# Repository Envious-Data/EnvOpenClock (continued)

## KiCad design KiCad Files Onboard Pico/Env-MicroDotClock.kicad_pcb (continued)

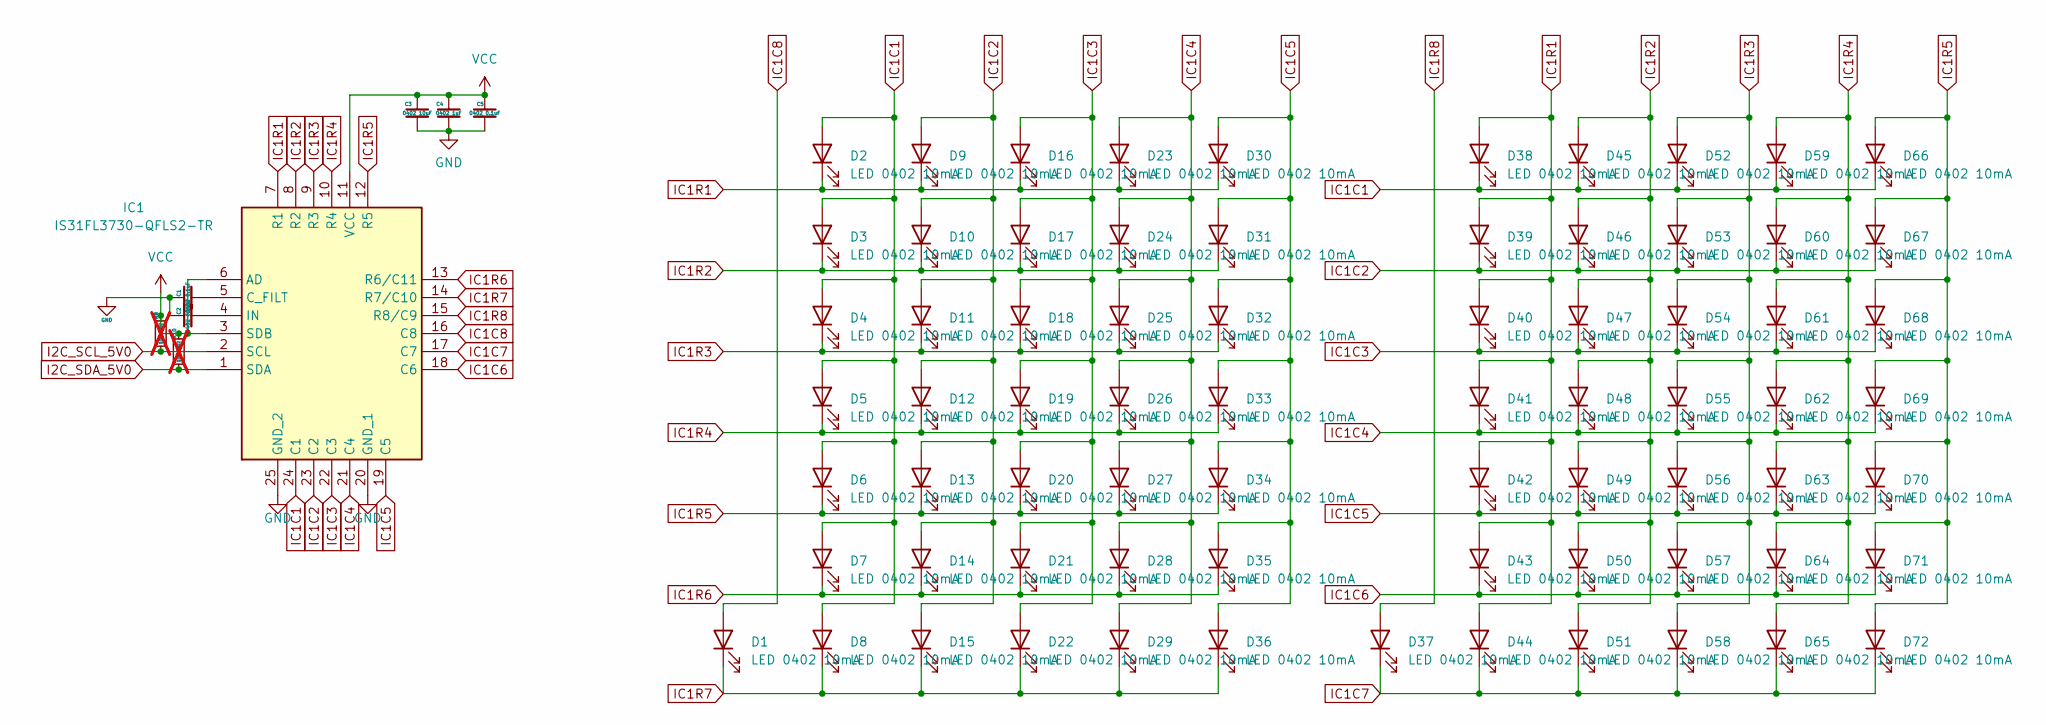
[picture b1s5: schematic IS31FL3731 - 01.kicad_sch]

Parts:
C1, C5: 0402 0.1uF; C_0402_1005Metric
C2: 0402 0.22uF; C_0402_1005Metric
C3: 0402 10uF; C_0402_1005Metric
C4: 0402 1uF; C_0402_1005Metric
D1, D2, D3, D4, D5, D6, D7, D8, D9, D10, D11, D12, D13, D14, D15, D16, D17, D18, D19, D20, D21, D22, D23, D24, D25, D26, D27, D28, D29, D30, D31, D32, D33, D34, D35, D36, D37, D38, D39, D40, D41, D42, D43, D44, D45, D46, D47, D48, D49, D50, D51, D52, D53, D54, D55, D56, D57, D58, D59, D60, D61, D62, D63, D64, D65, D66, D67, D68, D69, D70, D71, D72: LED 0402 10mA; LED_0402_1005Metric
IC1: IS31FL3730-QFLS2-TR; QFN-24-1EP_4x4mm_P0.5mm_EP2.6x2.6mm_ThermalVias; Mouser Part Number 870-IS31FL3730QFLS2R
R8, R10: 10K 0402; R_0402_1005Metric; not fitted

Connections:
GND: C1.1, C2.1, C3.2, C4.2, C5.2, IC1.20 (GND_1), IC1.25 (GND_2); also elsewhere on the board
I2C_SCL_5V0: IC1.2 (SCL), R8.1; also elsewhere on the board
I2C_SDA_5V0: IC1.1 (SDA), R10.1; also elsewhere on the board
IC1C1: D2.2 (A), D3.2 (A), D4.2 (A), D5.2 (A), D6.2 (A), D7.2 (A), D8.2 (A), D38.1 (K), D45.1 (K), D52.1 (K), D59.1 (K), D66.1 (K), IC1.24 (C1)
IC1C2: D9.2 (A), D10.2 (A), D11.2 (A), D12.2 (A), D13.2 (A), D14.2 (A), D15.2 (A), D39.1 (K), D46.1 (K), D53.1 (K), D60.1 (K), D67.1 (K), IC1.23 (C2)
IC1C3: D16.2 (A), D17.2 (A), D18.2 (A), D19.2 (A), D20.2 (A), D21.2 (A), D22.2 (A), D40.1 (K), D47.1 (K), D54.1 (K), D61.1 (K), D68.1 (K), IC1.22 (C3)
IC1C4: D23.2 (A), D24.2 (A), D25.2 (A), D26.2 (A), D27.2 (A), D28.2 (A), D29.2 (A), D41.1 (K), D48.1 (K), D55.1 (K), D62.1 (K), D69.1 (K), IC1.21 (C4)
IC1C5: D30.2 (A), D31.2 (A), D32.2 (A), D33.2 (A), D34.2 (A), D35.2 (A), D36.2 (A), D42.1 (K), D49.1 (K), D56.1 (K), D63.1 (K), D70.1 (K), IC1.19 (C5)
IC1C6: D43.1 (K), D50.1 (K), D57.1 (K), D64.1 (K), D71.1 (K), IC1.18 (C6)
IC1C7: D37.1 (K), D44.1 (K), D51.1 (K), D58.1 (K), D65.1 (K), D72.1 (K), IC1.17 (C7)
IC1C8: D1.2 (A), IC1.16 (C8)
IC1R1: D2.1 (K), D9.1 (K), D16.1 (K), D23.1 (K), D30.1 (K), D38.2 (A), D39.2 (A), D40.2 (A), D41.2 (A), D42.2 (A), D43.2 (A), D44.2 (A), IC1.7 (R1)
IC1R2: D3.1 (K), D10.1 (K), D17.1 (K), D24.1 (K), D31.1 (K), D45.2 (A), D46.2 (A), D47.2 (A), D48.2 (A), D49.2 (A), D50.2 (A), D51.2 (A), IC1.8 (R2)
IC1R3: D4.1 (K), D11.1 (K), D18.1 (K), D25.1 (K), D32.1 (K), D52.2 (A), D53.2 (A), D54.2 (A), D55.2 (A), D56.2 (A), D57.2 (A), D58.2 (A), IC1.9 (R3)
IC1R4: D5.1 (K), D12.1 (K), D19.1 (K), D26.1 (K), D33.1 (K), D59.2 (A), D60.2 (A), D61.2 (A), D62.2 (A), D63.2 (A), D64.2 (A), D65.2 (A), IC1.10 (R4)
IC1R5: D6.1 (K), D13.1 (K), D20.1 (K), D27.1 (K), D34.1 (K), D66.2 (A), D67.2 (A), D68.2 (A), D69.2 (A), D70.2 (A), D71.2 (A), D72.2 (A), IC1.12 (R5)
IC1R6: D7.1 (K), D14.1 (K), D21.1 (K), D28.1 (K), D35.1 (K), IC1.13 (R6/C11)
IC1R7: D1.1 (K), D8.1 (K), D15.1 (K), D22.1 (K), D29.1 (K), D36.1 (K), IC1.14 (R7/C10)
IC1R8: D37.2 (A), IC1.15 (R8/C9)
unnamed: C1.2, IC1.5 (C_FILT)
unnamed: C2.2, IC1.4 (IN)
VCC: C3.1, C4.1, C5.1, IC1.3 (SDB), IC1.6 (AD), IC1.11 (VCC), R8.2, R10.2; also elsewhere on the board

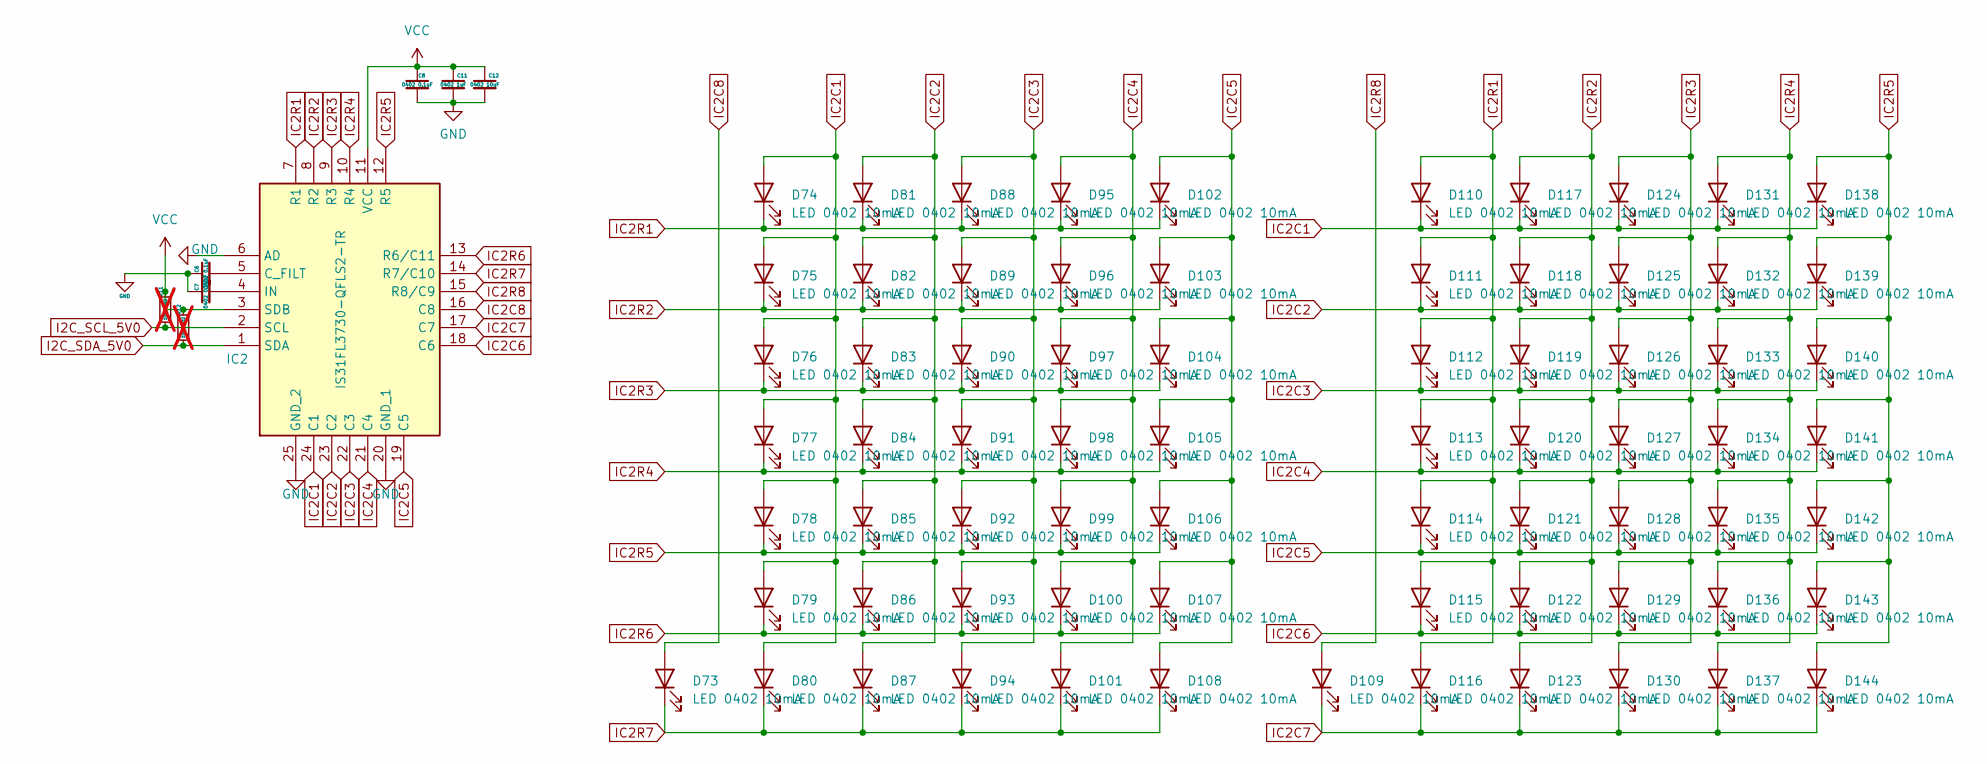
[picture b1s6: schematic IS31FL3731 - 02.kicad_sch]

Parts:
C6, C8: 0402 0.1uF; C_0402_1005Metric
C7: 0402 0.22uF; C_0402_1005Metric
C11: 0402 1uF; C_0402_1005Metric
C12: 0402 10uF; C_0402_1005Metric
D73, D74, D75, D76, D77, D78, D79, D80, D81, D82, D83, D84, D85, D86, D87, D88, D89, D90, D91, D92, D93, D94, D95, D96, D97, D98, D99, D100, D101, D102, D103, D104, D105, D106, D107, D108, D109, D110, D111, D112, D113, D114, D115, D116, D117, D118, D119, D120, D121, D122, D123, D124, D125, D126, D127, D128, D129, D130, D131, D132, D133, D134, D135, D136, D137, D138, D139, D140, D141, D142, D143, D144: LED 0402 10mA; LED_0402_1005Metric
IC2: IS31FL3730-QFLS2-TR; QFN-24-1EP_4x4mm_P0.5mm_EP2.6x2.6mm_ThermalVias; Mouser Part Number 870-IS31FL3730QFLS2R
R11, R12: 10K 0402; R_0402_1005Metric; not fitted

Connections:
GND: C6.1, C7.1, C8.2, C11.2, C12.2, IC2.6 (AD), IC2.20 (GND_1), IC2.25 (GND_2); also elsewhere on the board
I2C_SCL_5V0: IC2.2 (SCL), R11.1; also elsewhere on the board
I2C_SDA_5V0: IC2.1 (SDA), R12.1; also elsewhere on the board
IC2C1: D74.2 (A), D75.2 (A), D76.2 (A), D77.2 (A), D78.2 (A), D79.2 (A), D80.2 (A), D110.1 (K), D117.1 (K), D124.1 (K), D131.1 (K), D138.1 (K), IC2.24 (C1)
IC2C2: D81.2 (A), D82.2 (A), D83.2 (A), D84.2 (A), D85.2 (A), D86.2 (A), D87.2 (A), D111.1 (K), D118.1 (K), D125.1 (K), D132.1 (K), D139.1 (K), IC2.23 (C2)
IC2C3: D88.2 (A), D89.2 (A), D90.2 (A), D91.2 (A), D92.2 (A), D93.2 (A), D94.2 (A), D112.1 (K), D119.1 (K), D126.1 (K), D133.1 (K), D140.1 (K), IC2.22 (C3)
IC2C4: D95.2 (A), D96.2 (A), D97.2 (A), D98.2 (A), D99.2 (A), D100.2 (A), D101.2 (A), D113.1 (K), D120.1 (K), D127.1 (K), D134.1 (K), D141.1 (K), IC2.21 (C4)
IC2C5: D102.2 (A), D103.2 (A), D104.2 (A), D105.2 (A), D106.2 (A), D107.2 (A), D108.2 (A), D114.1 (K), D121.1 (K), D128.1 (K), D135.1 (K), D142.1 (K), IC2.19 (C5)
IC2C6: D115.1 (K), D122.1 (K), D129.1 (K), D136.1 (K), D143.1 (K), IC2.18 (C6)
IC2C7: D109.1 (K), D116.1 (K), D123.1 (K), D130.1 (K), D137.1 (K), D144.1 (K), IC2.17 (C7)
IC2C8: D73.2 (A), IC2.16 (C8)
IC2R1: D74.1 (K), D81.1 (K), D88.1 (K), D95.1 (K), D102.1 (K), D110.2 (A), D111.2 (A), D112.2 (A), D113.2 (A), D114.2 (A), D115.2 (A), D116.2 (A), IC2.7 (R1)
IC2R2: D75.1 (K), D82.1 (K), D89.1 (K), D96.1 (K), D103.1 (K), D117.2 (A), D118.2 (A), D119.2 (A), D120.2 (A), D121.2 (A), D122.2 (A), D123.2 (A), IC2.8 (R2)
IC2R3: D76.1 (K), D83.1 (K), D90.1 (K), D97.1 (K), D104.1 (K), D124.2 (A), D125.2 (A), D126.2 (A), D127.2 (A), D128.2 (A), D129.2 (A), D130.2 (A), IC2.9 (R3)
IC2R4: D77.1 (K), D84.1 (K), D91.1 (K), D98.1 (K), D105.1 (K), D131.2 (A), D132.2 (A), D133.2 (A), D134.2 (A), D135.2 (A), D136.2 (A), D137.2 (A), IC2.10 (R4)
IC2R5: D78.1 (K), D85.1 (K), D92.1 (K), D99.1 (K), D106.1 (K), D138.2 (A), D139.2 (A), D140.2 (A), D141.2 (A), D142.2 (A), D143.2 (A), D144.2 (A), IC2.12 (R5)
IC2R6: D79.1 (K), D86.1 (K), D93.1 (K), D100.1 (K), D107.1 (K), IC2.13 (R6/C11)
IC2R7: D73.1 (K), D80.1 (K), D87.1 (K), D94.1 (K), D101.1 (K), D108.1 (K), IC2.14 (R7/C10)
IC2R8: D109.2 (A), IC2.15 (R8/C9)
unnamed: C6.2, IC2.5 (C_FILT)
unnamed: C7.2, IC2.4 (IN)
VCC: C8.1, C11.1, C12.1, IC2.3 (SDB), IC2.11 (VCC), R11.2, R12.2; also elsewhere on the board

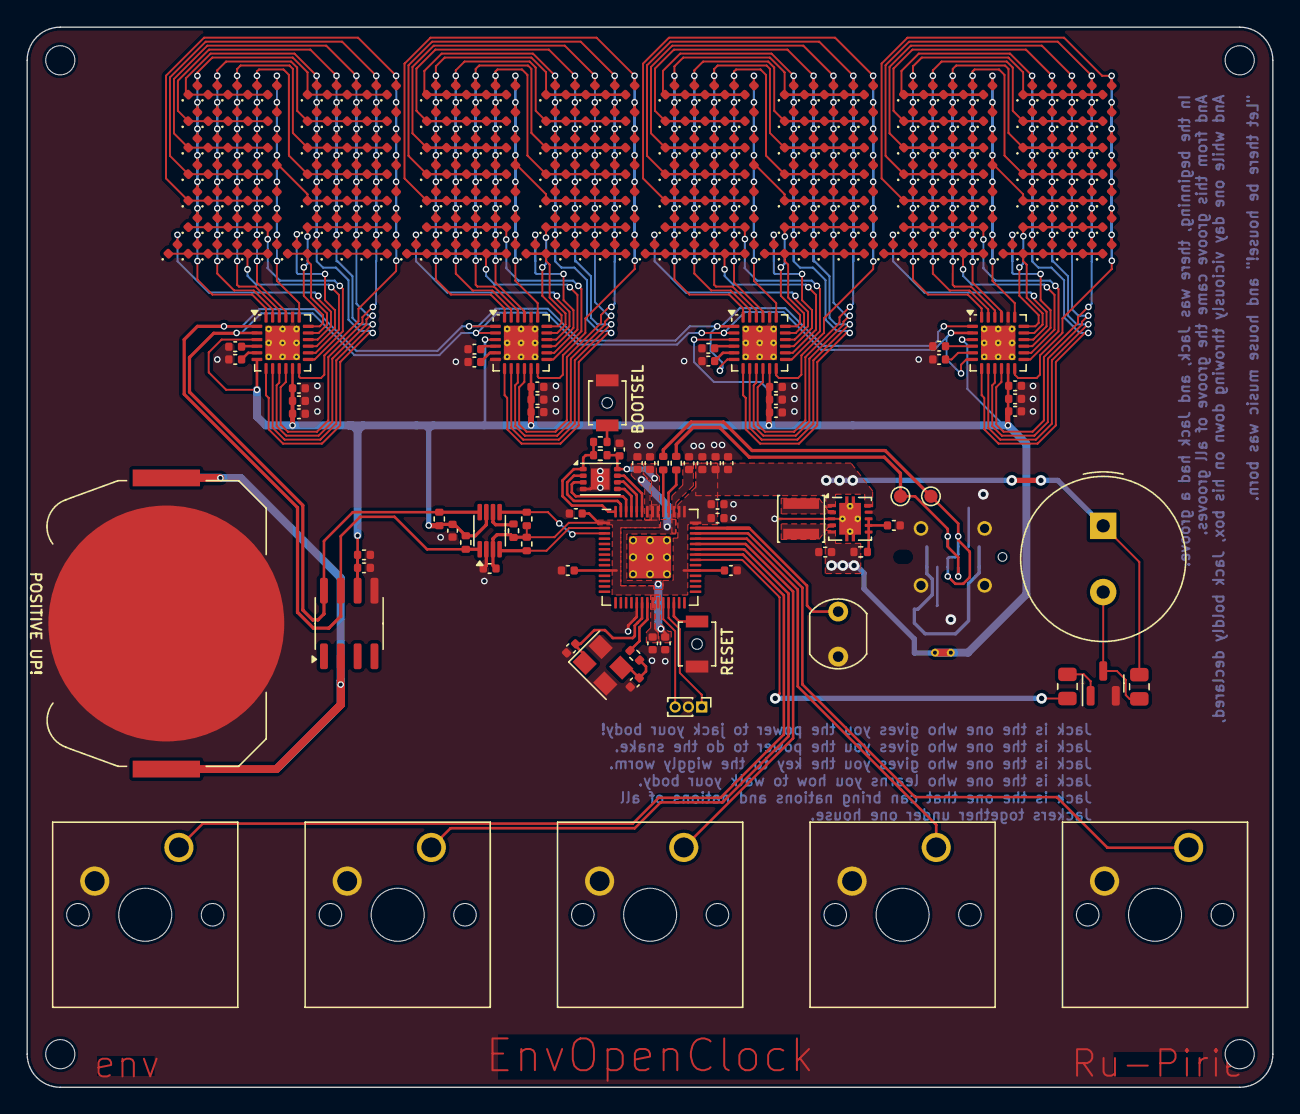
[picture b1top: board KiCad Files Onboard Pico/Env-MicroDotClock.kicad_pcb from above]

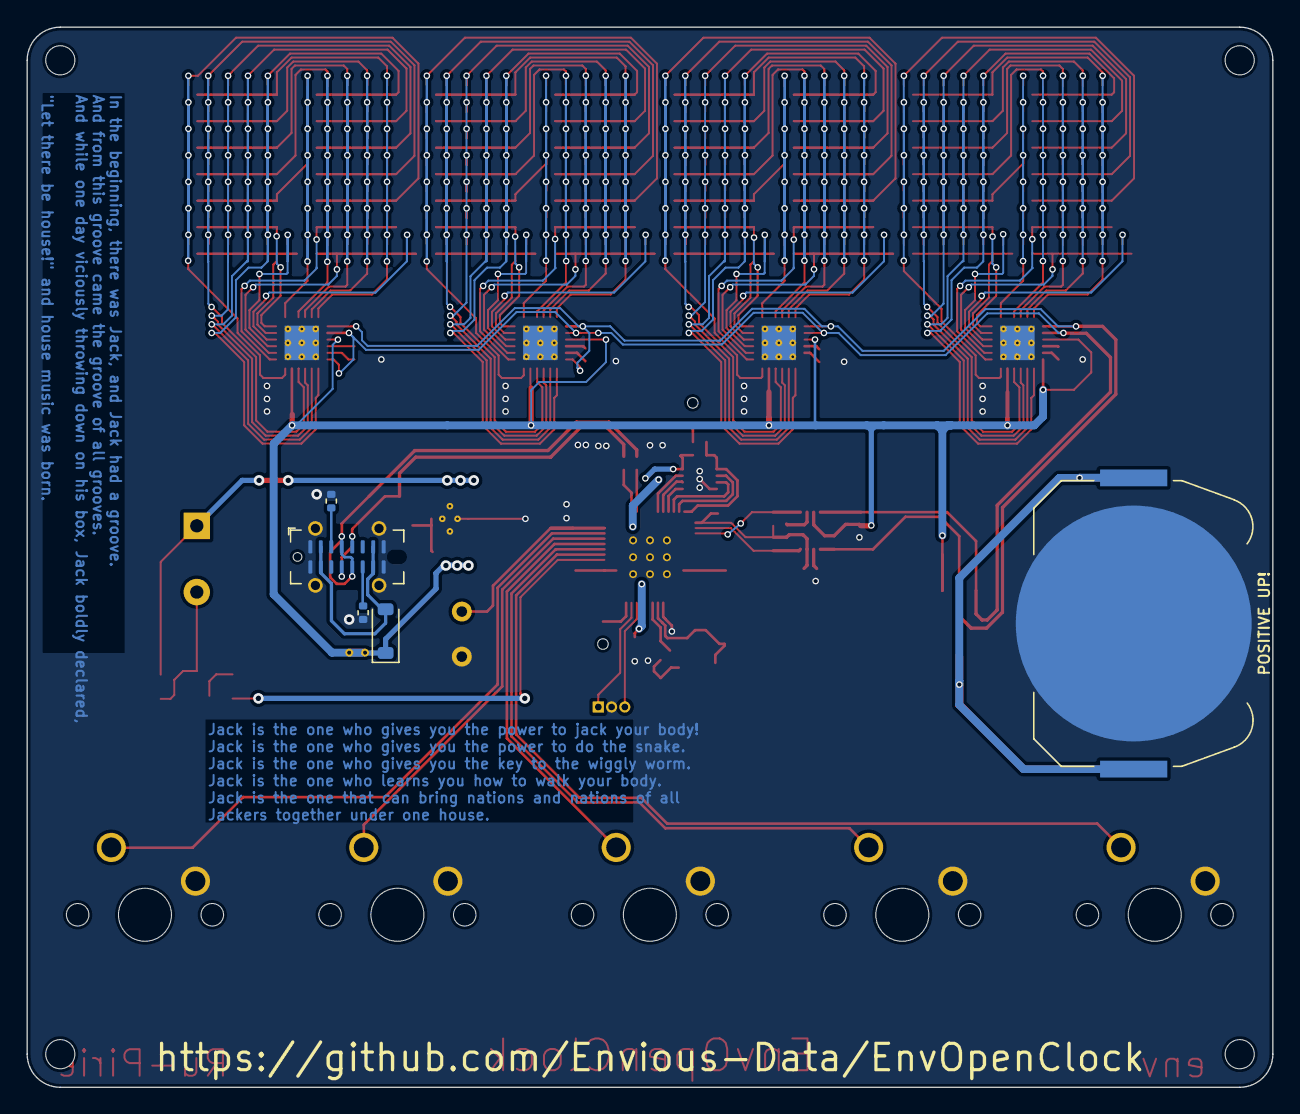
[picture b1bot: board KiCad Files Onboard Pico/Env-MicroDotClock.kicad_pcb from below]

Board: 2 copper layers, 94.0 x 80.0 mm, 378 parts (5 on the bottom side), 115 nets.

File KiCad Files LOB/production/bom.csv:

Designator,Footprint,Quantity,Value,LCSC Part #
BT1,BatteryHolder_Keystone_3034_1x20mm,1,Keystone 3034,
BZ1,Buzzer_TDK_PS1240P02BT_D12.2mm_H6.5mm,1,Buzzer 12.2Mm,
"C1, C3, C5, C7, C9",0402,5,0402 0.1uF,
"C10, C2, C4, C6, C8",0402,5,0402 1uF,
"D10, D100, D101, D102, D103, D104, D105, D106, D107, D108, D11, D110, D111, D112, D113, D114, D115, D116, D117, D118, D119, D12, D120, D121, D122, D123, D124, D125, D126, D127, D128, D129, D13, D130, D131, D132, D133, D134, D135, D136, D137, D138, D139, D14, D140, D141, D142, D143, D144, D146, D147, D148, D149, D15, D150, D151, D152, D153, D154, D155, D156, D157, D158, D159, D16, D160, D161, D162, D163, D164, D165, D166, D167, D168, D169, D17, D170, D171, D172, D173, D174, D175, D176, D177, D178, D179, D18, D180, D182, D183, D184, D185, D186, D187, D188, D189, D19, D190, D191, D192, D193, D194, D195, D196, D197, D198, D199, D2, D20, D200, D201, D202, D203, D204, D205, D206, D207, D208, D209, D21, D210, D211, D212, D213, D214, D215, D216, D218, D219, D22, D220, D221, D222, D223, D224, D225, D226, D227, D228, D229, D23, D230, D231, D232, D233, D234, D235, D236, D237, D238, D239, D24, D240, D241, D242, D243, D244, D245, D246, D247, D248, D249, D25, D250, D251, D252, D254, D255, D256, D257, D258, D259, D26, D260, D261, D262, D263, D264, D265, D266, D267, D268, D269, D27, D270, D271, D272, D273, D274, D275, D276, D277, D278, D279, D28, D280, D281, D282, D283, D284, D285, D286, D287, D288, D29, D3, D30, D31, D32, D33, D34, D35, D36, D38, D39, D4, D40, D41, D42, D43, D44, D45, D46, D47, D48, D49, D5, D50, D51, D52, D53, D54, D55, D56, D57, D58, D59, D6, D60, D61, D62, D63, D64, D65, D66, D67, D68, D69, D7, D70, D71, D72, D74, D75, D76, D77, D78, D79, D8, D80, D81, D82, D83, D84, D85, D86, D87, D88, D89, D9, D90, D91, D92, D93, D94, D95, D96, D97, D98, D99, DI1, DI2, DI3, DI4, DI5, DI6, DI7, DI8",0402,288,LED,
"H1, H2, H3, H4",MountingHole_2.2mm_M2,4,MountingHole,
"IC1, IC2, IC3, IC4",QFN-24-1EP_4x4mm_P0.5mm_EP2.6x2.6mm_ThermalVias,4,IS31FL3730-QFLS2-TR,
J1,PinHeader_1x06_P2.54mm_Vertical,1,Conn_01x06_Pin,
Q1,SOT-23,1,2SC1815,
"R1, R10, R11, R12, R2, R5, R6, R7, R8, R9",0402,10,0402 10K,
"R3, R4",0805,2,0805 1K,
"SW1, SW2, SW3, SW4, SW5, SW6",SW_Push_SPST_NO_Alps_SKRK,6,SW_SPST,
U1,RPi_Pico_SMD_TH,1,Raspberry Pi Pico,
U3,SOIC-16W_7.5x10.3mm_P1.27mm,1,DS3231M,

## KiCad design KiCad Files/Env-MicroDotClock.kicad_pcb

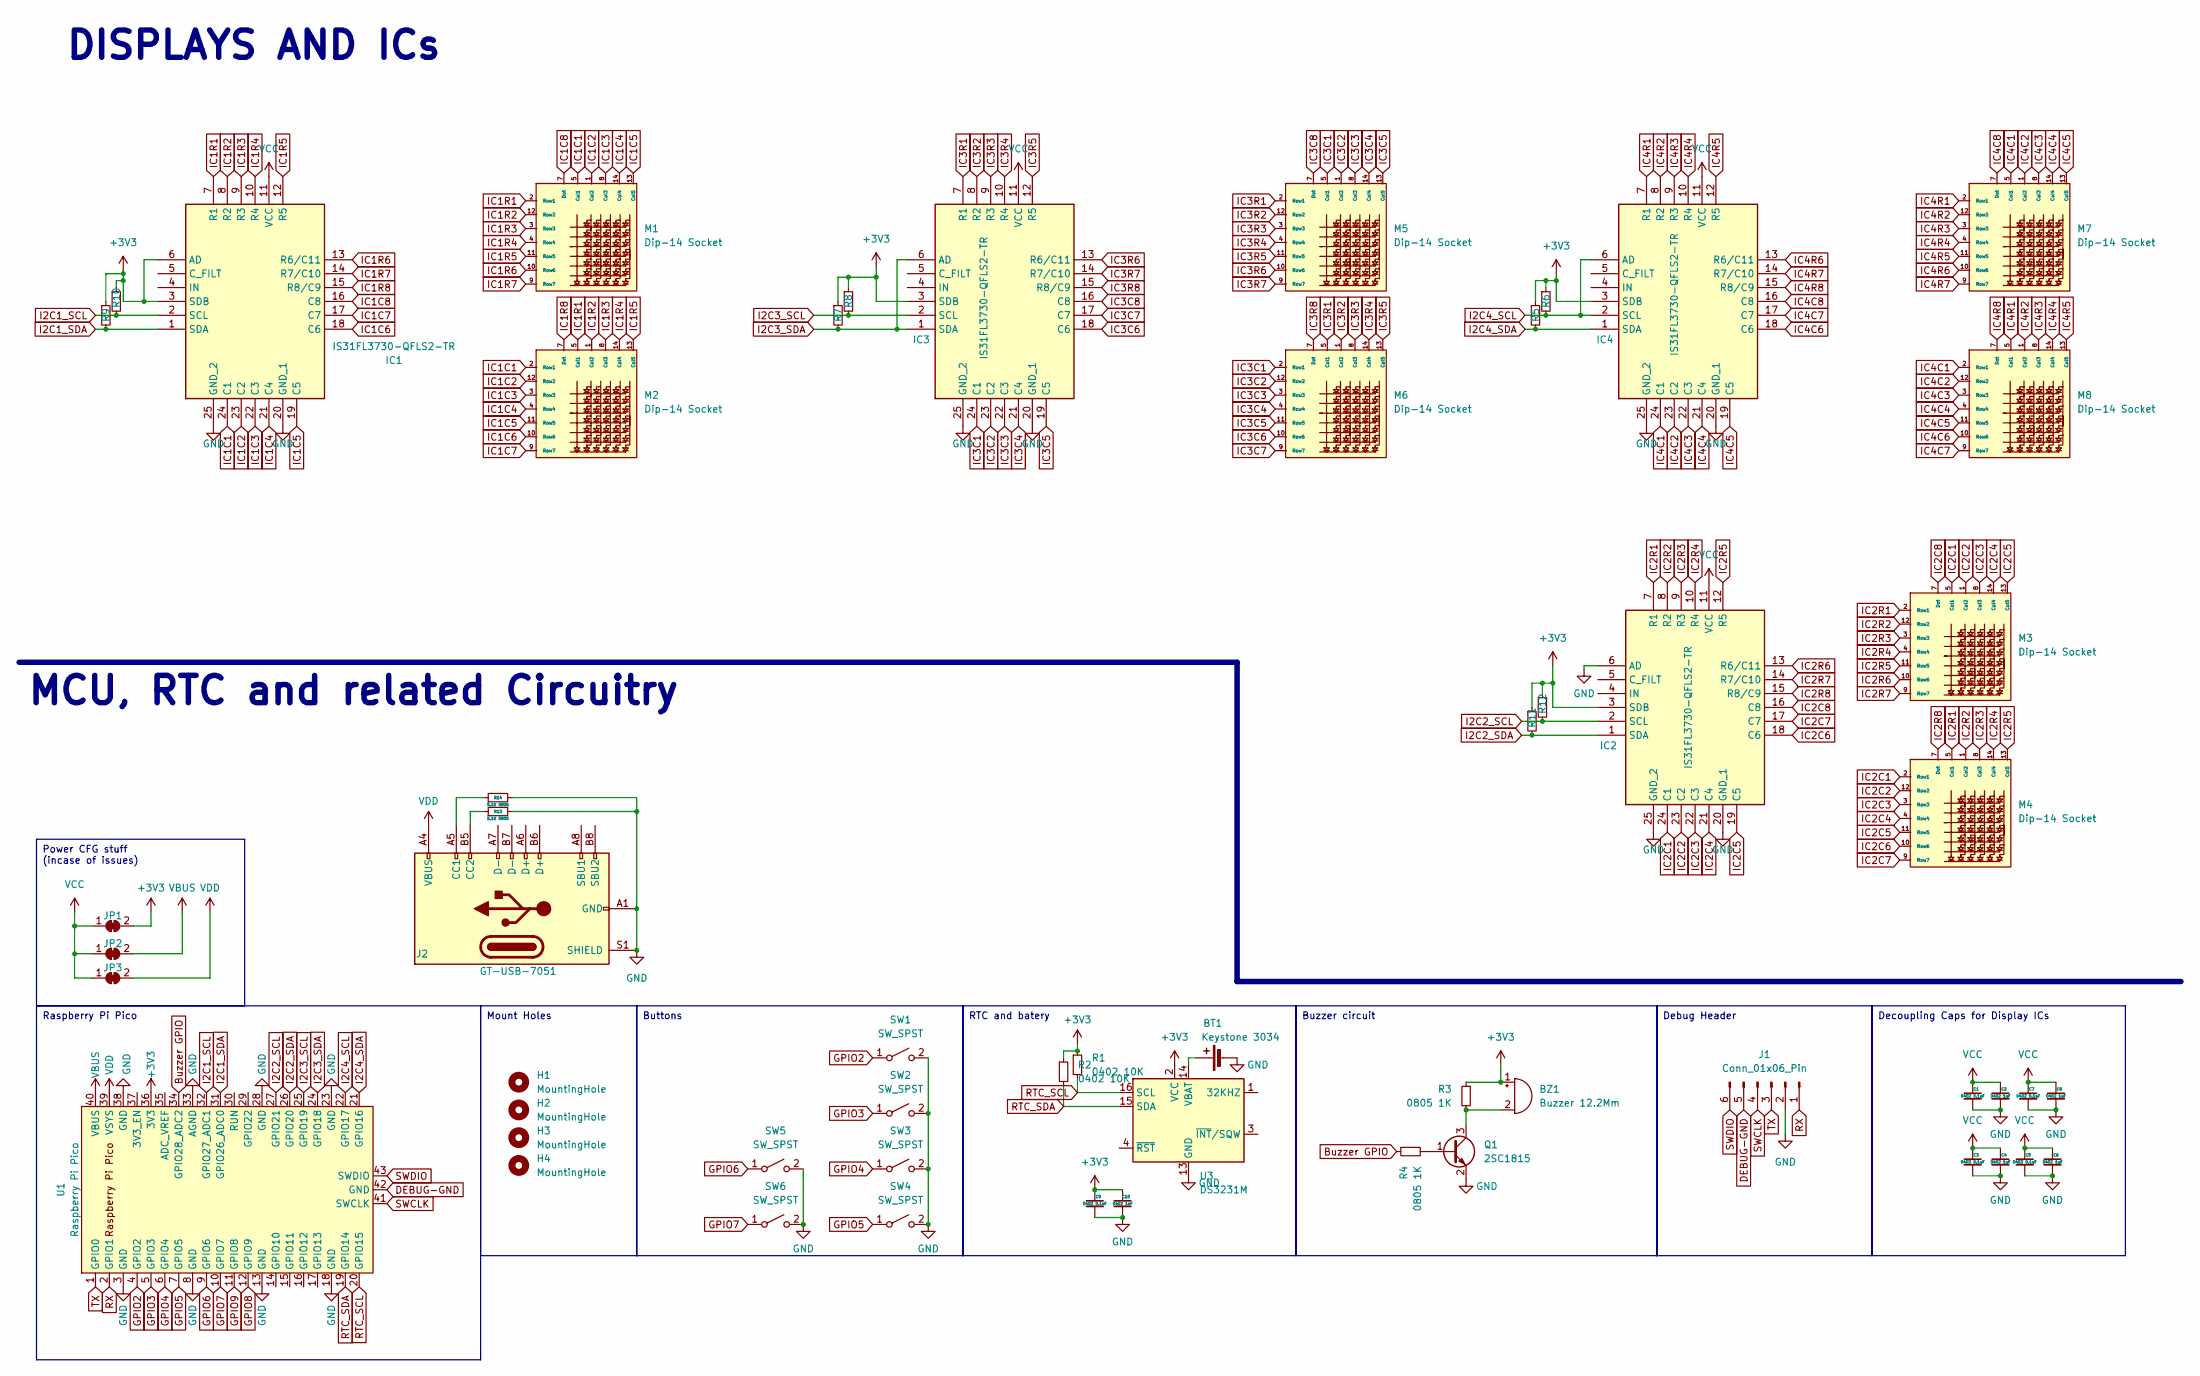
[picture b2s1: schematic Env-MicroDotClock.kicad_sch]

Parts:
BT1: Keystone 3034; BatteryHolder_Keystone_3034_1x20mm
BZ1: Buzzer 12.2Mm; Buzzer_TDK_PS1240P02BT_D12.2mm_H6.5mm
C1, C3, C5, C7, C9: 0402 0.1uF; C_0402_1005Metric
C2, C4, C6, C8, C10: 0402 1uF; C_0402_1005Metric
H1, H2, H3, H4: MountingHole; MountingHole_2.2mm_M2
IC1, IC2, IC3, IC4: IS31FL3730-QFLS2-TR; QFN-24-1EP_4x4mm_P0.5mm_EP2.6x2.6mm_ThermalVias; Mouser Part Number 870-IS31FL3730QFLS2R
J1: Conn_01x06_Pin; PinHeader_1x06_P2.54mm_Vertical
J2: GT-USB-7051; USB_C_Receptacle_G-Switch_GT-USB-7051x
JP1: bridge; SolderJumper-2_P1.3mm_Bridged_RoundedPad1.0x1.5mm
JP2, JP3: bridge; SolderJumper-2_P1.3mm_Open_RoundedPad1.0x1.5mm
M1, M2, M3, M4, M5, M6, M7, M8: Dip-14 Socket; DIP-14_W7.62mm_Socket
Q1: 2SC1815; SOT-23
R1, R2, R5, R6, R7, R8, R9, R10, R11, R12: 0402 10K; R_0402_1005Metric
R3, R4: 0805 1K; R_0805_2012Metric
R13, R14: 5.1K 0805; R_0805_2012Metric
SW1, SW2, SW3, SW4, SW5, SW6: SW_SPST; SW_Push_SPST_NO_Alps_SKRK
U1: Raspberry Pi Pico; RPi_Pico_SMD_TH
U3: DS3231M; SOIC-16W_7.5x10.3mm_P1.27mm

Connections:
+3V3: BZ1.1 (-), C9.1, C10.1, IC1.3 (SDB), IC1.6 (AD), IC2.3 (SDB), IC3.3 (SDB), IC4.3 (SDB), JP1.2 (B), R1.1, R2.1, R3.1, R5.1, R6.1, R7.1, R8.1, R9.1, R10.1, R11.1, R12.1, U1.36 (3V3), U3.2 (VCC)
Buzzer GPIO: R4.1, U1.34 (GPIO28_ADC2)
DEBUG-GND: J1.5, U1.42 (GND)
GND: BT1.2 (-), C1.2, C2.2, C3.2, C4.2, C5.2, C6.2, C7.2, C8.2, C9.2, C10.2, IC1.20 (GND_1), IC1.25 (GND_2), IC2.6 (AD), IC2.20 (GND_1), IC2.25 (GND_2), IC3.20 (GND_1), IC3.25 (GND_2), IC4.20 (GND_1), IC4.25 (GND_2), J1.2, J2.A1 (GND), J2.A12 (GND), J2.B1 (GND), J2.B12 (GND), J2.S1 (SHIELD), Q1.2 (E), R13.2, R14.2, SW1.2 (B), SW2.2 (B), SW3.2 (B), SW4.2 (B), SW5.2 (B), SW6.2 (B), U1.3 (GND), U1.8 (GND), U1.13 (GND), U1.18 (GND), U1.23 (GND), U1.28 (GND), U1.33 (AGND), U1.38 (GND), U3.5 (GND), U3.6 (GND), U3.7 (GND), U3.8 (GND), U3.9 (GND), U3.10 (GND), U3.11 (GND), U3.12 (GND), U3.13 (GND)
GPIO2: SW1.1 (A), U1.4 (GPIO2)
GPIO3: SW2.1 (A), U1.5 (GPIO3)
GPIO4: SW3.1 (A), U1.6 (GPIO4)
GPIO5: SW4.1 (A), U1.7 (GPIO5)
GPIO6: SW5.1 (A), U1.9 (GPIO6)
GPIO7: SW6.1 (A), U1.10 (GPIO7)
GPIO8: U1.12 (GPIO9)
GPIO9: U1.11 (GPIO8)
I2C1_SCL: IC1.2 (SCL), R10.2, U1.32 (GPIO27_ADC1)
I2C1_SDA: IC1.1 (SDA), R9.2, U1.31 (GPIO26_ADC0)
I2C2_SCL: IC2.2 (SCL), R12.2, U1.27 (GPIO21)
I2C2_SDA: IC2.1 (SDA), R11.2, U1.26 (GPIO20)
I2C3_SCL: IC3.2 (SCL), R8.2, U1.25 (GPIO19)
I2C3_SDA: IC3.1 (SDA), IC3.6 (AD), R7.2, U1.24 (GPIO18)
I2C4_SCL: IC4.2 (SCL), IC4.6 (AD), R6.2, U1.22 (GPIO17)
I2C4_SDA: IC4.1 (SDA), R5.2, U1.21 (GPIO16)
IC1C1: IC1.24 (C1), M1.5 (Col1), M2.2 (Row1)
IC1C2: IC1.23 (C2), M1.1 (Col2), M2.12 (Row2)
IC1C3: IC1.22 (C3), M1.8 (Col3), M2.3 (Row3)
IC1C4: IC1.21 (C4), M1.14 (Col4), M2.4 (Row4)
IC1C5: IC1.19 (C5), M1.13 (Col5), M2.11 (Row5)
IC1C6: IC1.18 (C6), M2.10 (Row6)
IC1C7: IC1.17 (C7), M2.9 (Row7)
IC1C8: IC1.16 (C8), M1.7 (Dot)
IC1R1: IC1.7 (R1), M1.2 (Row1), M2.5 (Col1)
IC1R2: IC1.8 (R2), M1.12 (Row2), M2.1 (Col2)
IC1R3: IC1.9 (R3), M1.3 (Row3), M2.8 (Col3)
IC1R4: IC1.10 (R4), M1.4 (Row4), M2.14 (Col4)
IC1R5: IC1.12 (R5), M1.11 (Row5), M2.13 (Col5)
IC1R6: IC1.13 (R6/C11), M1.10 (Row6)
IC1R7: IC1.14 (R7/C10), M1.9 (Row7)
IC1R8: IC1.15 (R8/C9), M2.7 (Dot)
IC2C1: IC2.24 (C1), M3.5 (Col1), M4.2 (Row1)
IC2C2: IC2.23 (C2), M3.1 (Col2), M4.12 (Row2)
IC2C3: IC2.22 (C3), M3.8 (Col3), M4.3 (Row3)
IC2C4: IC2.21 (C4), M3.14 (Col4), M4.4 (Row4)
IC2C5: IC2.19 (C5), M3.13 (Col5), M4.11 (Row5)
IC2C6: IC2.18 (C6), M4.10 (Row6)
IC2C7: IC2.17 (C7), M4.9 (Row7)
IC2C8: IC2.16 (C8), M3.7 (Dot)
IC2R1: IC2.7 (R1), M3.2 (Row1), M4.5 (Col1)
IC2R2: IC2.8 (R2), M3.12 (Row2), M4.1 (Col2)
IC2R3: IC2.9 (R3), M3.3 (Row3), M4.8 (Col3)
IC2R4: IC2.10 (R4), M3.4 (Row4), M4.14 (Col4)
IC2R5: IC2.12 (R5), M3.11 (Row5), M4.13 (Col5)
IC2R6: IC2.13 (R6/C11), M3.10 (Row6)
IC2R7: IC2.14 (R7/C10), M3.9 (Row7)
IC2R8: IC2.15 (R8/C9), M4.7 (Dot)
IC3C1: IC3.24 (C1), M5.5 (Col1), M6.2 (Row1)
IC3C2: IC3.23 (C2), M5.1 (Col2), M6.12 (Row2)
IC3C3: IC3.22 (C3), M5.8 (Col3), M6.3 (Row3)
IC3C4: IC3.21 (C4), M5.14 (Col4), M6.4 (Row4)
IC3C5: IC3.19 (C5), M5.13 (Col5), M6.11 (Row5)
IC3C6: IC3.18 (C6), M6.10 (Row6)
IC3C7: IC3.17 (C7), M6.9 (Row7)
IC3C8: IC3.16 (C8), M5.7 (Dot)
IC3R1: IC3.7 (R1), M5.2 (Row1), M6.5 (Col1)
IC3R2: IC3.8 (R2), M5.12 (Row2), M6.1 (Col2)
IC3R3: IC3.9 (R3), M5.3 (Row3), M6.8 (Col3)
IC3R4: IC3.10 (R4), M5.4 (Row4), M6.14 (Col4)
IC3R5: IC3.12 (R5), M5.11 (Row5), M6.13 (Col5)
IC3R6: IC3.13 (R6/C11), M5.10 (Row6)
IC3R7: IC3.14 (R7/C10), M5.9 (Row7)
IC3R8: IC3.15 (R8/C9), M6.7 (Dot)
IC4C1: IC4.24 (C1), M7.5 (Col1), M8.2 (Row1)
IC4C2: IC4.23 (C2), M7.1 (Col2), M8.12 (Row2)
IC4C3: IC4.22 (C3), M7.8 (Col3), M8.3 (Row3)
IC4C4: IC4.21 (C4), M7.14 (Col4), M8.4 (Row4)
IC4C5: IC4.19 (C5), M7.13 (Col5), M8.11 (Row5)
IC4C6: IC4.18 (C6), M8.10 (Row6)
IC4C7: IC4.17 (C7), M8.9 (Row7)
IC4C8: IC4.16 (C8), M7.7 (Dot)
IC4R1: IC4.7 (R1), M7.2 (Row1), M8.5 (Col1)
IC4R2: IC4.8 (R2), M7.12 (Row2), M8.1 (Col2)
IC4R3: IC4.9 (R3), M7.3 (Row3), M8.8 (Col3)
IC4R4: IC4.10 (R4), M7.4 (Row4), M8.14 (Col4)
IC4R5: IC4.12 (R5), M7.11 (Row5), M8.13 (Col5)
IC4R6: IC4.13 (R6/C11), M7.10 (Row6)
IC4R7: IC4.14 (R7/C10), M7.9 (Row7)
IC4R8: IC4.15 (R8/C9), M8.7 (Dot)
unnamed: BT1.1 (+), U3.14 (VBAT)
unnamed: BZ1.2 (+), Q1.3 (C), R3.2
unnamed: J2.A5 (CC1), R14.1
unnamed: J2.B5 (CC2), R13.1
unnamed: Q1.1 (B), R4.2
RTC_SCL: R1.2, U1.20 (GPIO15), U3.16 (SCL)
RTC_SDA: R2.2, U1.19 (GPIO14), U3.15 (SDA)
RX: J1.1, U1.2 (GPIO1)
SWCLK: J1.4, U1.41 (SWCLK)
SWDIO: J1.6, U1.43 (SWDIO)
TX: J1.3, U1.1 (GPIO0)
VBUS: JP2.2 (B), U1.40 (VBUS)
VCC: C1.1, C2.1, C3.1, C4.1, C5.1, C6.1, C7.1, C8.1, IC1.11 (VCC), IC2.11 (VCC), IC3.11 (VCC), IC4.11 (VCC), JP1.1 (A), JP2.1 (A), JP3.1 (A)
VDD: J2.A4 (VBUS), J2.A9 (VBUS), J2.B4 (VBUS), J2.B9 (VBUS), JP3.2 (B), U1.39 (VSYS)

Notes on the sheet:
Raspberry Pi Pico
RTC and batery
Mount Holes
Power CFG stuff (incase of issues)
Buzzer circuit
Debug Header
Decoupling Caps for Display ICs
Buttons
DISPLAYS AND ICs
MCU, RTC and related Circuitry

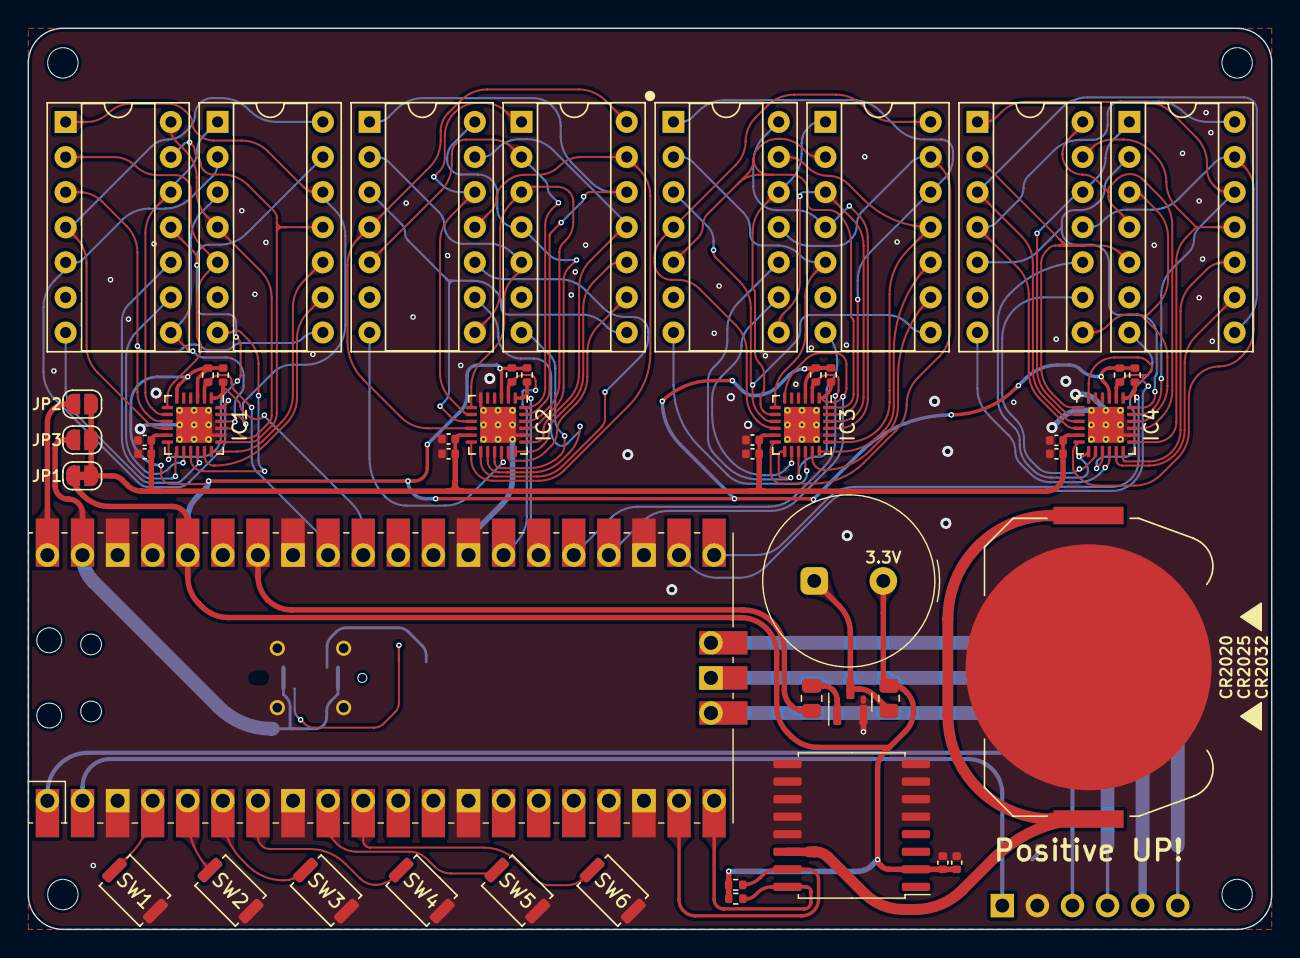
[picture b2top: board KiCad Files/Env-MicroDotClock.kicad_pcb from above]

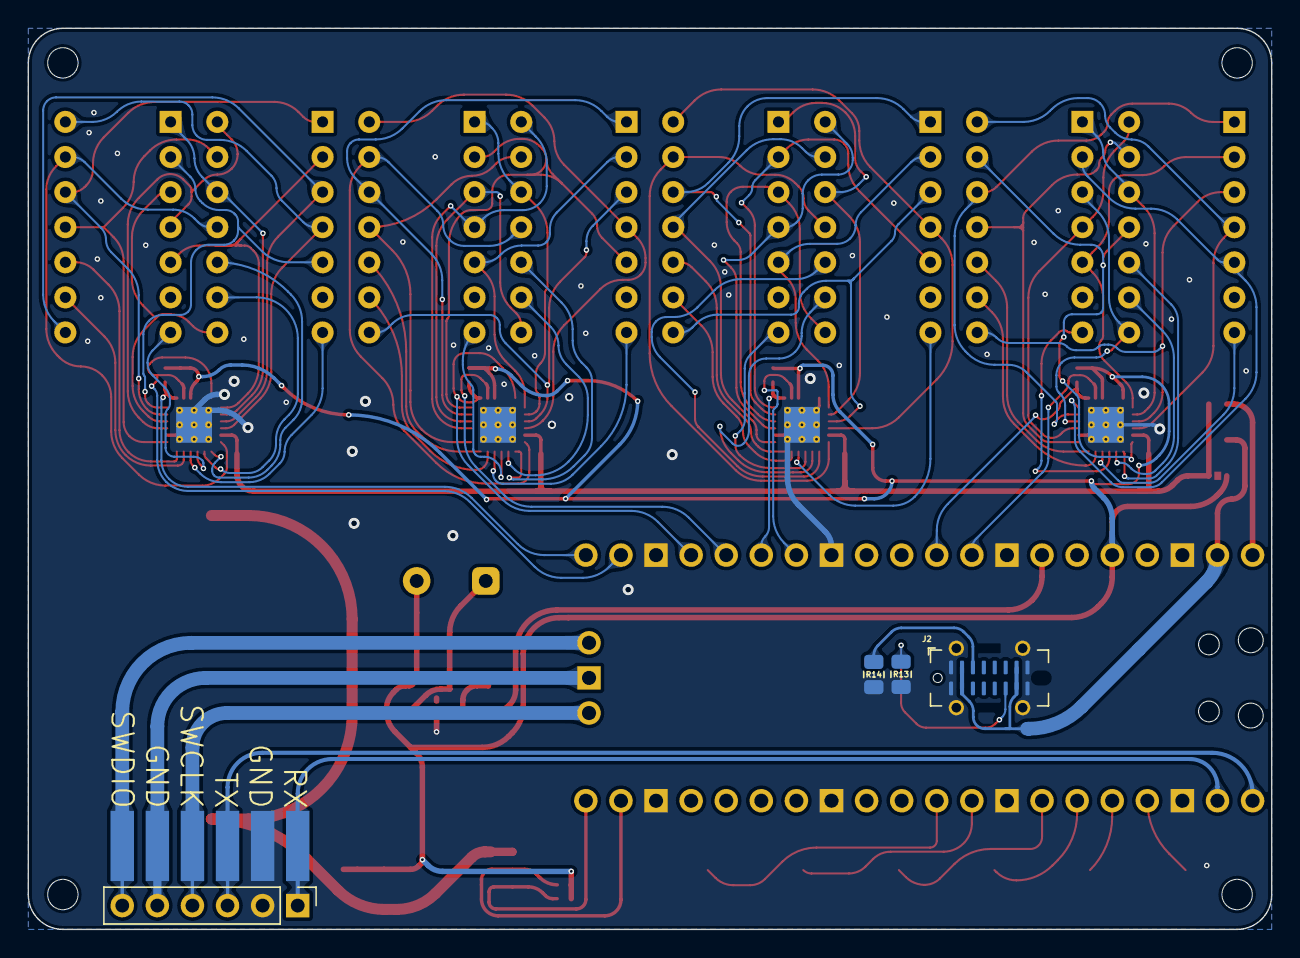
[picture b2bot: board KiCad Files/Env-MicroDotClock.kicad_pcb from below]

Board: 2 copper layers, 90.0 x 65.2 mm, 56 parts (4 on the bottom side), 96 nets.

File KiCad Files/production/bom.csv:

Designator,Footprint,Quantity,Value,LCSC Part #
BT1,BatteryHolder_Keystone_3034_1x20mm,1,Keystone 3034,
BZ1,Buzzer_TDK_PS1240P02BT_D12.2mm_H6.5mm,1,Buzzer 12.2Mm,
"C1, C3, C5, C7, C9",0402,5,0402 0.1uF,
"C10, C2, C4, C6, C8",0402,5,0402 1uF,
"H1, H2, H3, H4",MountingHole_2.2mm_M2,4,MountingHole,
"IC1, IC2, IC3, IC4",QFN-24-1EP_4x4mm_P0.5mm_EP2.6x2.6mm_ThermalVias,4,IS31FL3730-QFLS2-TR,
"M1, M2, M3, M4, M5, M6, M7, M8",DIP-14_W7.62mm_Socket,8,Dip-14 Socket,
Q1,SOT-23,1,2SC1815,
"R1, R10, R11, R12, R2, R5, R6, R7, R8, R9",0402,10,0402 10K,
"R3, R4",0805,2,0805 1K,
"SW1, SW2, SW3, SW4",SW_Push_SPST_NO_Alps_SKRK,4,SKRK,
U1,RPi_Pico_SMD_TH,1,Raspberry Pi Pico,
U3,SOIC-16W_7.5x10.3mm_P1.27mm,1,DS3231M,
